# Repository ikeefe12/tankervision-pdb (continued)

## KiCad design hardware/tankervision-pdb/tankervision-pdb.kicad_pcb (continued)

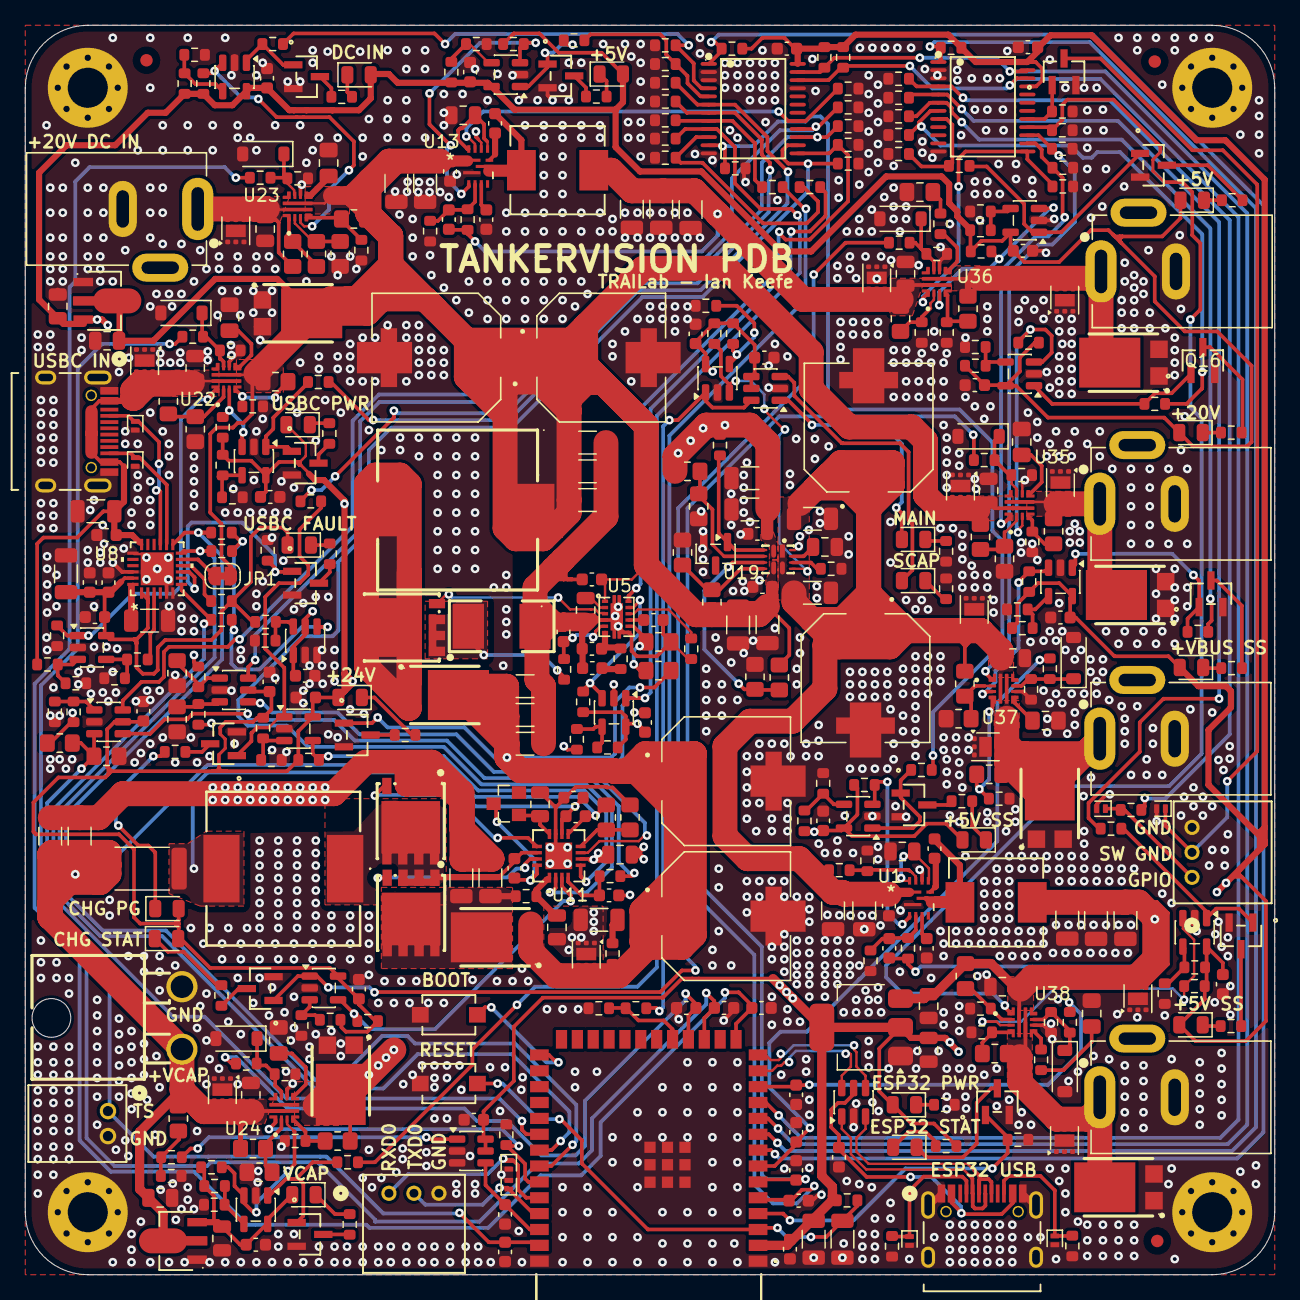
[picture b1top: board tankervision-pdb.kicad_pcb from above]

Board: 4 copper layers, 100.0 x 100.0 mm, 452 parts (0 on the bottom side), 234 nets.

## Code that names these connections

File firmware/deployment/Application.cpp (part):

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    json.add("}");
  }
  json.add("},\"signals\":{");
  const char *names[] = {"PG_USB","PG_DC","VCAP_PG","SCC_PG","SCC_STAT","24V_VBUS_PG","5V_VBUS_PG","5V_SS_PG",
    "EXT_VBUS_PG","EXT_5V_VBUS_PG","EXT_SS_PG","EXT_5V_SS_PG","JET_ON_FB","PMUX_ST","VCAP_EN","STAT_LED",
    "CTRL_IN_INT_N","CTRL_EXT_INT_N","PD_INT","24V_VBUS_EN","SCC_EN","SCC_ISET_SW","SCC_TS_SW","5V_VBUS_EN",
    "EXT_VBUS_EN","EXT_5V_VBUS_EN","EXT_SS_EN","EXT_5V_SS_EN","JET_PWR_BTN_CTRL","BOOT_N"};
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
